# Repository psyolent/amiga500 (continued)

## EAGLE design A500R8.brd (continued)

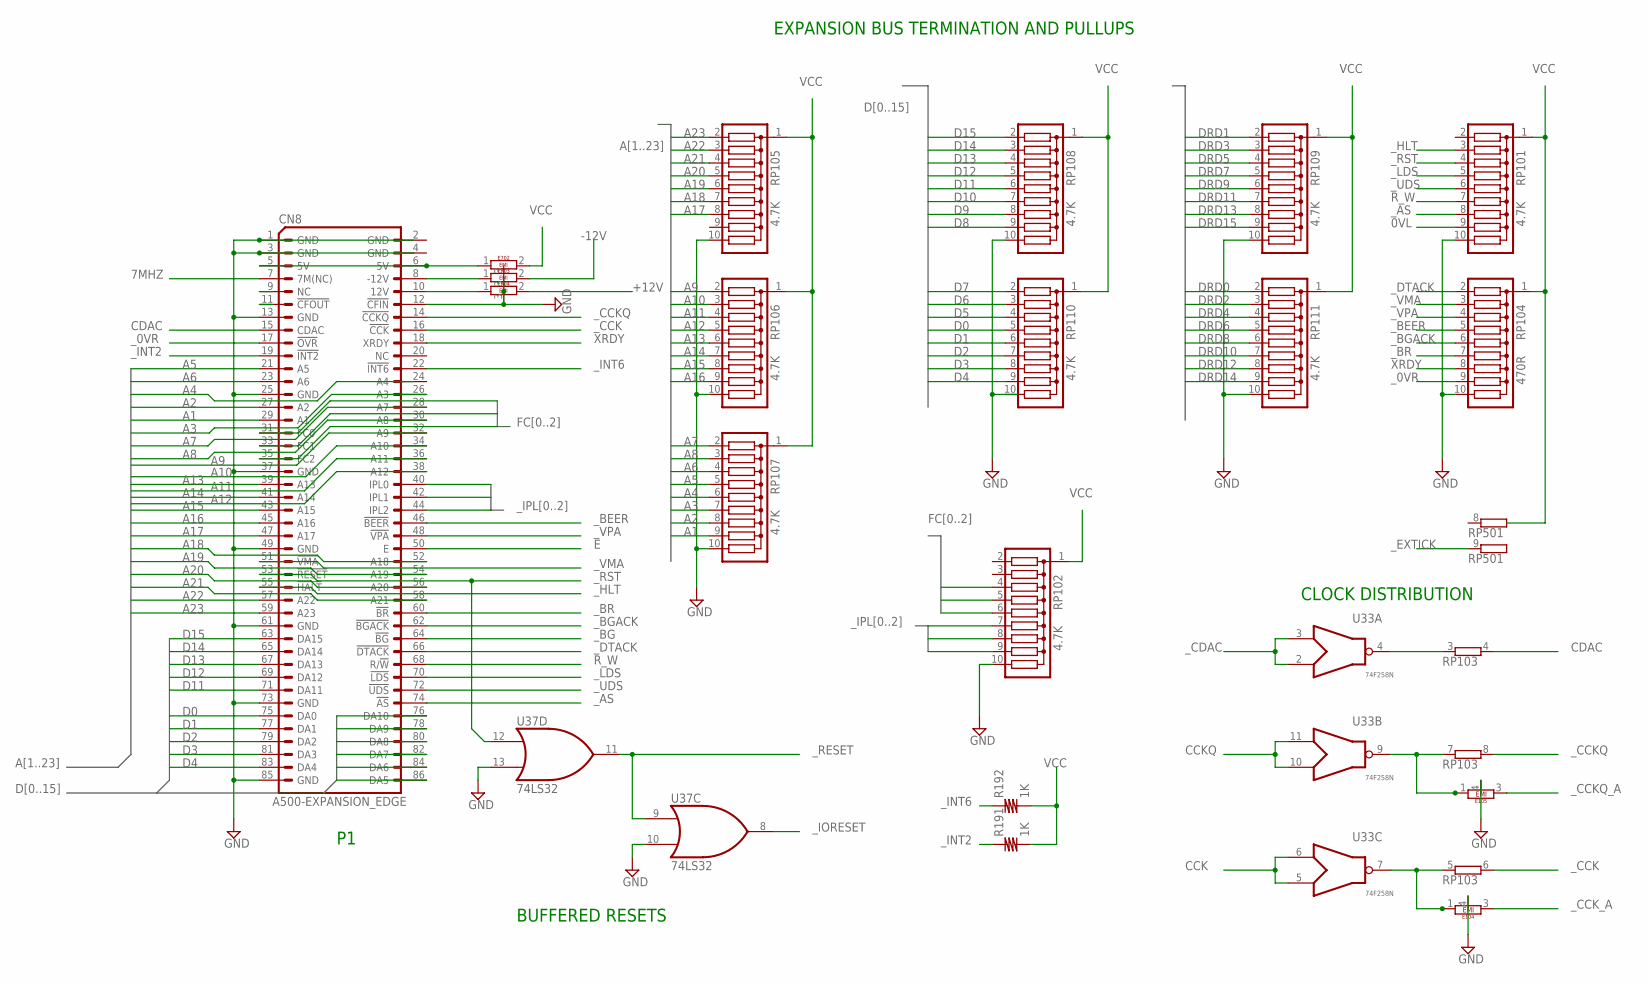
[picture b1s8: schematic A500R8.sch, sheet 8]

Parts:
CN8: A500-EXPANSION_EDGE; LKONT_43
E104, E105: EMIFILTERLONG; EMIFILTLONG
E702, E703, E704: EMIFILTER
R191, R192: 1K; R10B4
RP101, RP102, RP105, RP106, RP107, RP108, RP109, RP110, RP111: 4.7K; SIL10
RP103: E5RP; SIL10
RP104: 470R; SIL10
RP501: GE09RP; SIL10
U33: 74F258N; DIL16
U37: 74LS32; DIL14

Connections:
0VL: RP101.9; also elsewhere on the board
7MHZ: CN8.7 (7M(NC)); also elsewhere on the board
+12V: E704.2; also elsewhere on the board
-12V: E703.2; also elsewhere on the board
A1: CN8.29 (A1), RP107.9; also elsewhere on the board
A2: CN8.27 (A2), RP107.8; also elsewhere on the board
A3: CN8.26 (A3), RP107.7; also elsewhere on the board
A4: RP107.6; also elsewhere on the board
A5: CN8.21 (A5), RP107.5; also elsewhere on the board
A6: CN8.23 (A6), RP107.4; also elsewhere on the board
A7: CN8.28 (A7), RP107.2; also elsewhere on the board
A8: CN8.30 (A8), RP107.3; also elsewhere on the board
A9: CN8.32 (A9), RP106.2; also elsewhere on the board
A10: CN8.34 (A10), RP106.3; also elsewhere on the board
A11: CN8.36 (A11), RP106.4; also elsewhere on the board
A12: CN8.38 (A12), RP106.5; also elsewhere on the board
A13: CN8.39 (A13), RP106.6; also elsewhere on the board
A14: CN8.41 (A14), RP106.7; also elsewhere on the board
A15: CN8.43 (A15), RP106.8; also elsewhere on the board
A16: CN8.45 (A16), RP106.9; also elsewhere on the board
A17: CN8.47 (A17), RP105.8; also elsewhere on the board
A18: CN8.52 (A18), RP105.7; also elsewhere on the board
A19: CN8.54 (A19), RP105.6; also elsewhere on the board
A20: CN8.56 (A20), RP105.5; also elsewhere on the board
A21: CN8.58 (A21), RP105.4; also elsewhere on the board
A22: CN8.57 (A22), RP105.3; also elsewhere on the board
A23: CN8.59 (A23), RP105.2; also elsewhere on the board
CCK: U33.5 (I1), U33.6 (I0); also elsewhere on the board
CCKQ: U33.10 (I1), U33.11 (I0); also elsewhere on the board
CDAC: CN8.15 (CDAC), RP103.4 (2); also elsewhere on the board
D0: CN8.75 (DA0), RP110.5; also elsewhere on the board
D1: CN8.77 (DA1), RP110.6; also elsewhere on the board
D2: CN8.79 (DA2), RP110.7; also elsewhere on the board
D3: CN8.81 (DA3), RP110.8; also elsewhere on the board
D4: CN8.83 (DA4), RP110.9; also elsewhere on the board
D5: CN8.86 (DA5), RP110.4; also elsewhere on the board
D6: CN8.84 (DA6), RP110.3; also elsewhere on the board
D7: CN8.82 (DA7), RP110.2; also elsewhere on the board
D8: CN8.80 (DA8), RP108.9; also elsewhere on the board
D9: CN8.78 (DA9), RP108.8; also elsewhere on the board
D10: CN8.76 (DA10), RP108.7; also elsewhere on the board
D11: CN8.71 (DA11), RP108.6; also elsewhere on the board
D12: CN8.69 (DA12), RP108.5; also elsewhere on the board
D13: CN8.67 (DA13), RP108.4; also elsewhere on the board
D14: CN8.65 (DA14), RP108.3; also elsewhere on the board
D15: CN8.63 (DA15), RP108.2; also elsewhere on the board
DRD0: RP111.2; also elsewhere on the board
DRD1: RP109.2; also elsewhere on the board
DRD2: RP111.3; also elsewhere on the board
DRD3: RP109.3; also elsewhere on the board
DRD4: RP111.4; also elsewhere on the board
DRD5: RP109.4; also elsewhere on the board
DRD6: RP111.5; also elsewhere on the board
DRD7: RP109.5; also elsewhere on the board
DRD8: RP111.6; also elsewhere on the board
DRD9: RP109.6; also elsewhere on the board
DRD10: RP111.7; also elsewhere on the board
DRD11: RP109.7; also elsewhere on the board
DRD12: RP111.8; also elsewhere on the board
DRD13: RP109.8; also elsewhere on the board
DRD14: RP111.9; also elsewhere on the board
DRD15: RP109.9; also elsewhere on the board
E: CN8.50 (E); also elsewhere on the board
FC0: CN8.31 (FC0), RP102.4; also elsewhere on the board
FC1: CN8.33 (FC1), RP102.5; also elsewhere on the board
FC2: CN8.35 (FC2), RP102.6; also elsewhere on the board
GND: CN8.1 (GND), CN8.3 (GND), CN8.12 (!CFIN!), CN8.13 (GND), CN8.25 (GND), CN8.37 (GND), CN8.49 (GND), CN8.61 (GND), CN8.73 (GND), CN8.85 (GND), E104.4, E105.4, E702.3, E703.3, E704.3, RP101.10, RP102.10, RP104.10, RP105.10, RP106.10, RP107.10, RP108.10, RP109.10, RP111.10, U37.10 (I1), U37.13 (I1); also elsewhere on the board
unnamed: CN8.5 (5V), CN8.6 (5V), E702.1
unnamed: RP103.3 (1), U33.4 (O)
unnamed: CN8.8 (-12V), E703.1
unnamed: CN8.10 (12V), E704.1
unnamed: E105.1, E105.2, RP103.7 (1), U33.9 (O)
unnamed: E104.1, E104.2, RP103.5 (1), U33.7 (O)
R_W: CN8.68 (R/!W!), RP101.7; also elsewhere on the board
VCC: E702.2, R191.2, R192.2, RP101.1, RP102.1, RP104.1, RP105.1, RP106.1, RP107.1, RP108.1, RP109.1, RP110.1, RP111.1; also elsewhere on the board
XRDY: CN8.18 (XRDY), RP104.8; also elsewhere on the board
_0VR: CN8.17 (!OVR!), RP104.9; also elsewhere on the board
_AS: CN8.74 (!AS!), RP101.8; also elsewhere on the board
_BEER: CN8.46 (!BEER!), RP104.5; also elsewhere on the board
_BG: CN8.64 (!BG!); also elsewhere on the board
_BGACK: CN8.62 (!BGACK!), RP104.6; also elsewhere on the board
_BR: CN8.60 (!BR!), RP104.7; also elsewhere on the board
_CCK: CN8.16 (!CCK!), RP103.6 (2); also elsewhere on the board
_CCKQ: CN8.14 (!CCKQ!), RP103.8 (2); also elsewhere on the board
_CCKQ_A: E105.3; also elsewhere on the board
_CCK_A: E104.3; also elsewhere on the board
_CDAC: U33.2 (I1), U33.3 (I0); also elsewhere on the board
_DTACK: CN8.66 (!DTACK!), RP104.2; also elsewhere on the board
_EXTICK: RP501.9 (2); also elsewhere on the board
_HLT: CN8.55 (!HALT!), RP101.3; also elsewhere on the board
_INT2: CN8.19 (!INT2!), R191.1; also elsewhere on the board
_INT6: CN8.22 (!INT6!), R192.1; also elsewhere on the board
_IORESET: U37.8 (O); also elsewhere on the board
_IPL0: CN8.40 (IPL0), RP102.7; also elsewhere on the board
_IPL1: CN8.42 (IPL1), RP102.8; also elsewhere on the board
_IPL2: CN8.44 (IPL2), RP102.9; also elsewhere on the board
_LDS: CN8.70 (!LDS!), RP101.5; also elsewhere on the board
_RESET: U37.9 (I0), U37.11 (O); also elsewhere on the board
_RST: CN8.53 (!RESET!), RP101.4, U37.12 (I0); also elsewhere on the board
_UDS: CN8.72 (!UDS!), RP101.6; also elsewhere on the board
_VMA: CN8.51 (!VMA!), RP104.3; also elsewhere on the board
_VPA: CN8.48 (!VPA!), RP104.4; also elsewhere on the board

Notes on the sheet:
BUFFERED RESETS
EXPANSION BUS TERMINATION AND PULLUPS
CLOCK DISTRIBUTION

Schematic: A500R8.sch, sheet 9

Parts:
C1, C2, C5, C6, C11, C13, C14: 0.33uF; C10B4
C7, C8, C10, C12, C15, C32, C34, C35, C36, C37, C800, C801, C802, C803: 0.1uF; C10B4
C33: .01uF; C10B4
C804: 33uF; C10B4
C811, C812, C813, C814, C815, C816: 100uF; E5-6
C821, C822: 47uF; E5-6
E101, E407: .01uF; EMIFILTER
E102, E106, E107, E108, E109, E791, E792, E793, E794: 47pF; R10B4
E103: 47pF; C10B4
LF1: AMIGALINEFILTER; DK31
RP103: E5RP; SIL10
U1: MC68000P; DIL64
U2: AGNU8375; PLCC84
U5: GARY; DIP48-6
U6: 1/2MB_ROM27C800; DIP42-6
U7, U8: 8520 CIA; DIP40-6
U10, U12: 74LS244; DIL20
U11, U13: 74LS373; DIL20
U15: 74LS157N; DIL16
U32: 74F139; DIL16
U33: 74F258N; DIL16
U34: 74F373; DIL20
U35: 74F244; DIL20
U36: 74LS05N; DIL14
U37: 74LS32; DIL14
X3: MAB5SH

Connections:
7MHZ: E103.2; also elsewhere on the board
7MHZ_A: E794.2; also elsewhere on the board
+5: C800.2, LF1.2, X3.1
+12: LF1.4, X3.3
+12V: C802.1, C821.+, LF1.5; also elsewhere on the board
-12: LF1.3, X3.5
-12V: C803.2, C822.-, LF1.6; also elsewhere on the board
CCK: E108.2; also elsewhere on the board
CCKQ: E107.2; also elsewhere on the board
CDAC: E793.2; also elsewhere on the board
GND: C1.2, C2.2, C5.2, C6.2, C7.2, C8.2, C10.2, C11.2, C12.2, C13.2, C14.2, C15.2, C32.2, C33.2, C34.2, C35.2, C36.2, C37.2, C801.2, C802.2, C803.1, C804.2, C811.-, C812.-, C813.-, C814.-, C815.-, C816.-, C821.-, C822.+, E101.3, E102.1, E103.1, E106.1, E107.1, E108.1, E109.1, E407.3, E791.1, E792.1, E793.1, E794.1, LF1.8, U1.16 (GND), U1.53 (GND), U2.41 (GND), U2.58 (GND), U2.82 (GND), U5.1 (GND), U5.24 (GND), U5.40 (GND), U6.12 (GND), U6.31 (GND), U7.1 (GND1), U8.1 (GND1), U10.10 (GND), U11.10 (GND), U12.10 (GND), U13.10 (GND), U15.8 (GND), U32.8 (GND), U33.8 (GND), U34.10 (GND), U35.10 (GND), U36.7 (GND), U37.7 (GND), X3.2; also elsewhere on the board
unnamed: C2.1, E101.2, U2.15 (VCC)
unnamed: C33.1, E407.2, U33.16 (VCC)
PE: X3.PE, X3.PE@ (PE)
P_GND: C800.1, LF1.1, X3.4
VCC: C1.1, C5.1, C6.1, C7.1, C8.1, C10.1, C11.1, C12.1, C13.1, C14.1, C15.1, C32.1, C34.1, C35.1, C36.1, C37.1, C801.1, C804.1, C811.+, C812.+, C813.+, C814.+, C815.+, C816.+, E101.1, E407.1, LF1.7, U1.14 (VCC), U1.49 (VCC), U5.6 (VCC), U5.17 (VCC), U5.48 (VCC), U6.22 (VCC), U7.20 (VCC1), U8.20 (VCC1), U10.20 (VCC), U11.20 (VCC), U12.20 (VCC), U13.20 (VCC), U15.16 (VCC), U32.16 (VCC), U34.20 (VCC), U35.20 (VCC), U36.14 (VCC), U37.14 (VCC); also elsewhere on the board
_CCK: E792.2; also elsewhere on the board
_CCKQ: E791.2; also elsewhere on the board
_CCKQ_A: E109.2; also elsewhere on the board
_CCK_A: E102.2; also elsewhere on the board
_CDAC: E106.2; also elsewhere on the board

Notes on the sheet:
SPARES
X1 is on Schematic 1
FCC GOOBERS

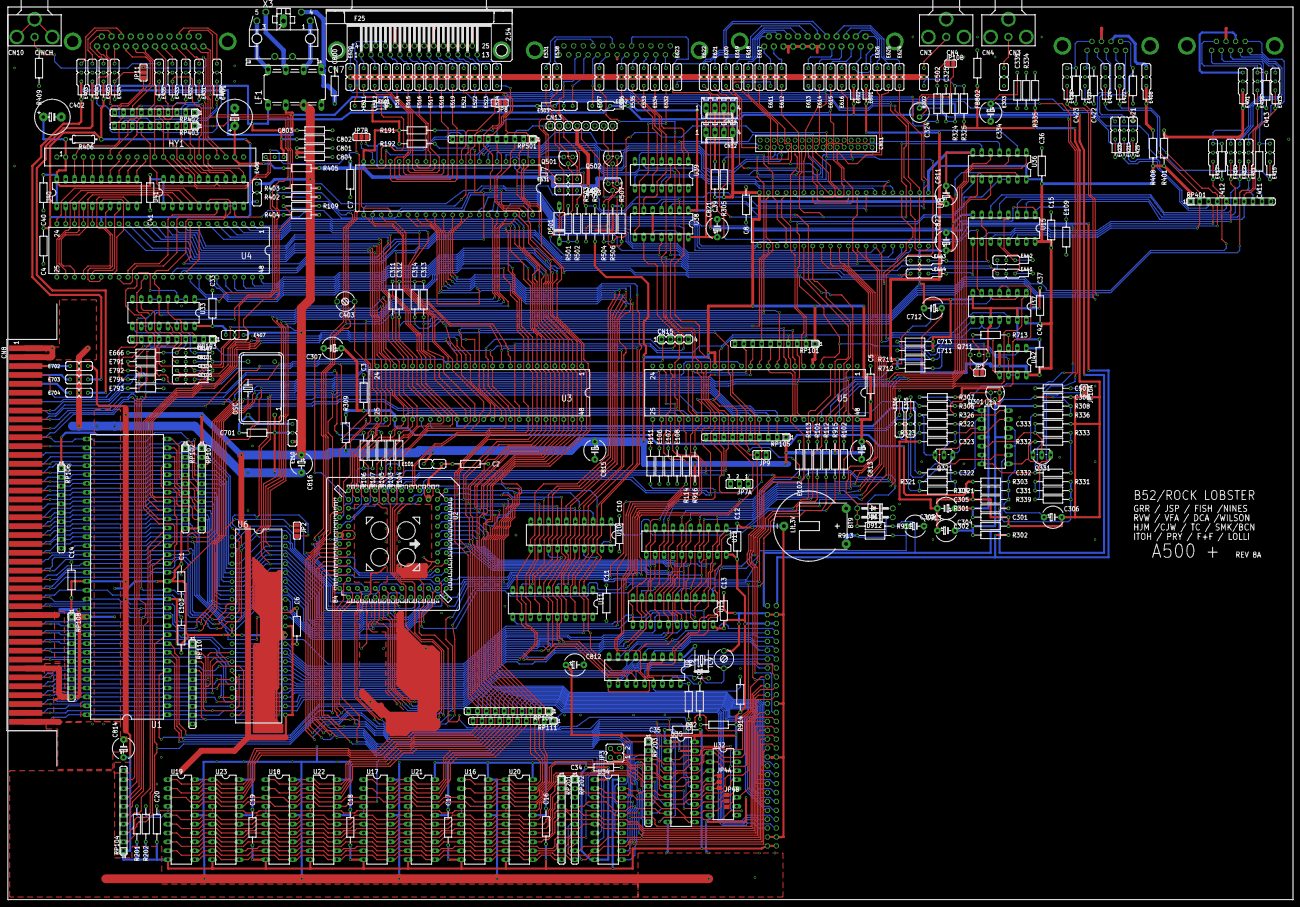
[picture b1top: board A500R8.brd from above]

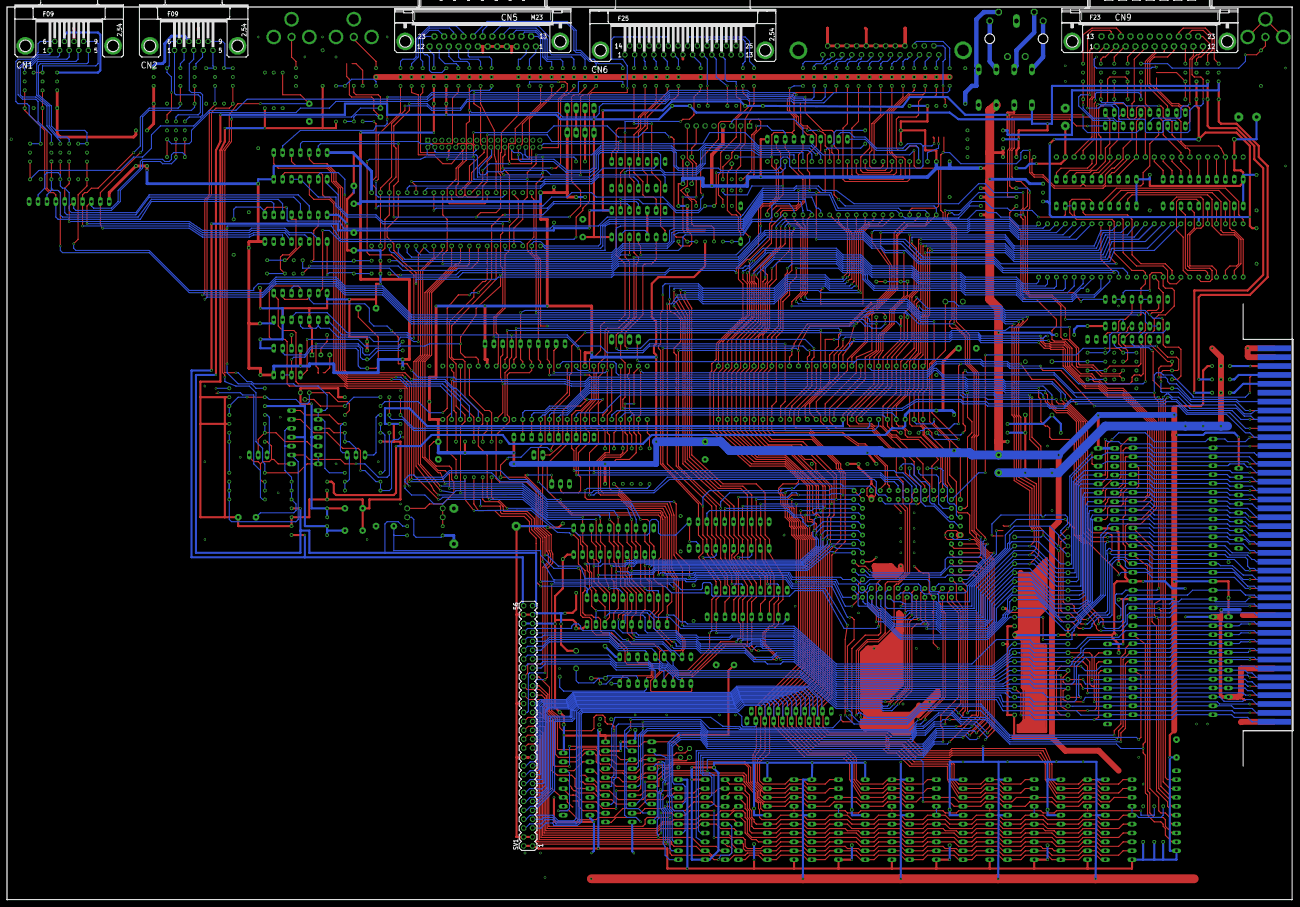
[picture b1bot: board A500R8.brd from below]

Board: 2 copper layers, 367.3 x 254.9 mm, 342 parts (6 on the bottom side), 463 nets.

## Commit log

2019-05-26 Amiga 500v8 Initial Release v0.1
2019-06-04 Create LICENSE
